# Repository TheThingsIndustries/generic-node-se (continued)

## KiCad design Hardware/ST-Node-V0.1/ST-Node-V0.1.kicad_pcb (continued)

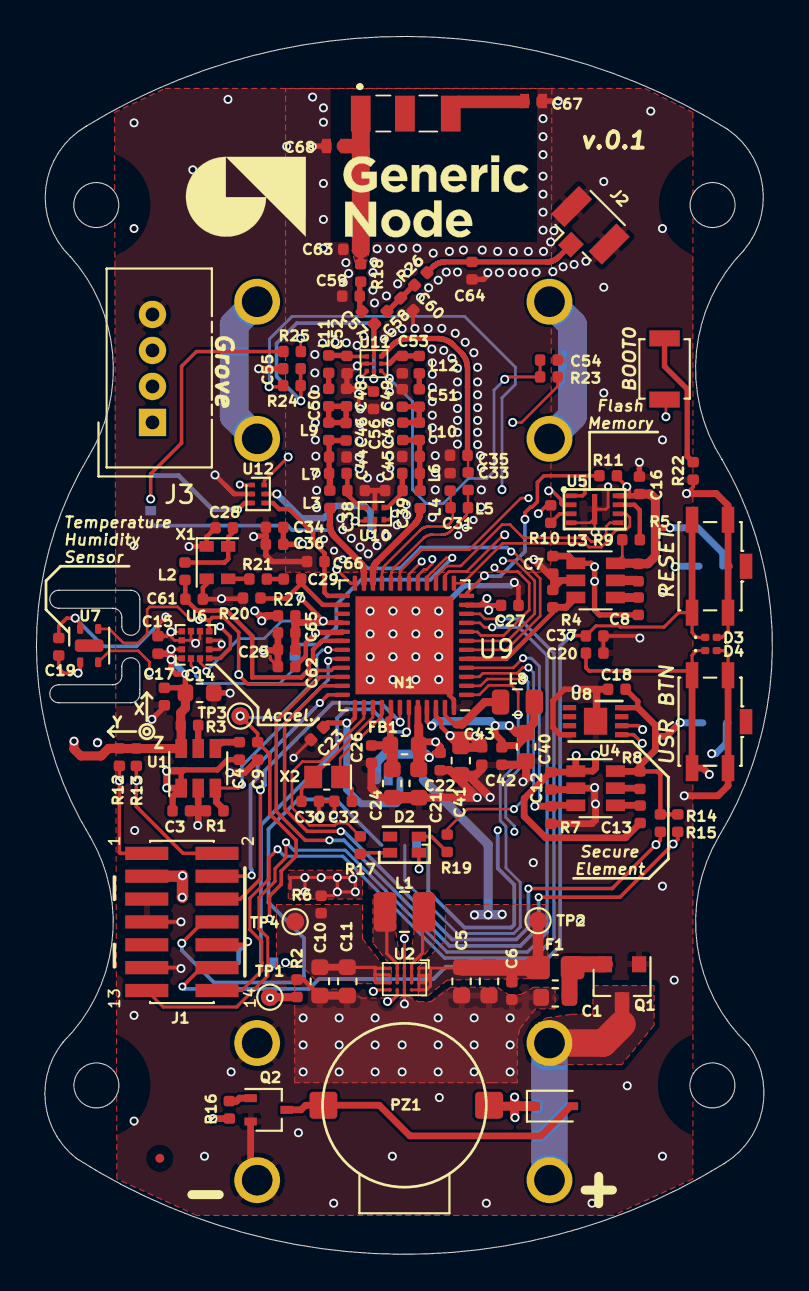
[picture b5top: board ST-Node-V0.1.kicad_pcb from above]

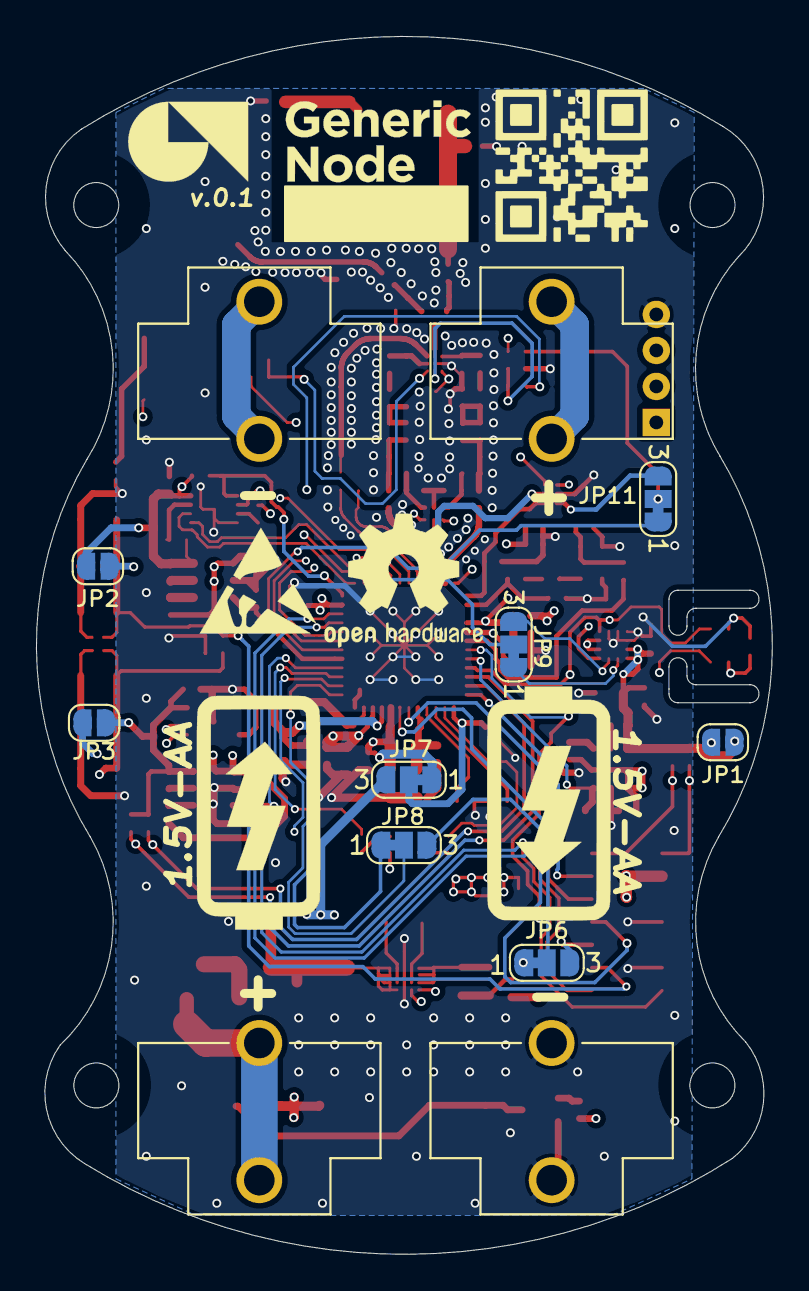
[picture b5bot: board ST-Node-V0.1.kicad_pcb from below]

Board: 4 copper layers, 40.9 x 67.7 mm, 159 parts (12 on the bottom side), 97 nets.

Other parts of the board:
J3: Grove_I2C; NS-Tech_Grove_1x04_P2mm_Vertical
R27: 0R; R_0402_1005Metric

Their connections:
/LoRa MCU/I2C1_SCL: J3.1; also elsewhere on the board
/LoRa MCU/I2C1_SDA: J3.2; also elsewhere on the board
/Peripherals/VCC_SENSORS: J3.3; also elsewhere on the board
GND: J3.4; also elsewhere on the board

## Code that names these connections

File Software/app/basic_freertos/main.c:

/** Copyright © 2021 The Things Industries B.V.
 *
 * Licensed under the Apache License, Version 2.0 (the "License");
 * you may not use this file except in compliance with the License.
 * You may obtain a copy of the License at
 *
 *     http://www.apache.org/licenses/LICENSE-2.0
 *
 * Unless required by applicable law or agreed to in writing, software
 * distributed under the License is distributed on an "AS IS" BASIS,
 * WITHOUT WARRANTIES OR CONDITIONS OF ANY KIND, either express or implied.
 * See the License for the specific language governing permissions and
 * limitations under the License.
 */

/**
 * @file main.c
 *
 * @copyright Copyright (c) 2021 The Things Industries B.V.
 *
 */

#include "app.h"
#include "cmsis_os.h"
#include "FreeRTOS_iot_log_task.h"

uint32_t osQueueMsg;
uint32_t Queue_value = 100;

/* Definitions for TxThread */
osThreadId_t TxThreadHandle;
const osThreadAttr_t TxThread_attributes = {
    .name = "TxThread",
    .priority = (osPriority_t)osPriorityBelowNormal,
    .stack_size = 512 * 4};

/* Definitions for RxThread */
osThreadId_t RxThreadHandle;
const osThreadAttr_t RxThread_attributes = {
    .name = "RxThread",
    .priority = (osPriority_t)osPriorityNormal,
    .stack_size = 512 * 4};

/* Definitions for osqueue */
osMessageQueueId_t osqueueHandle;
const osMessageQueueAttr_t osqueue_attributes = {
    .name = "osqueue"};

static void SystemClock_Config(void);
static void Error_Handler(void);

void QueueSendThread(void *argument);
void QueueReceiveThread(void *argument);

static void MX_GPIO_Init(void);

/**
  * @brief  Function implementing the TxThread thread.
  * @param  argument: Not used
  * @retval None
  */
void QueueSendThread(void *argument)
{
  for (;;)
  {
#if (GNSE_TINY_TRACER_ENABLE)
    configPRINTF(("\r\n Send a Tx msg \r\n"));
#endif
    /* Place this thread into the blocked state until it is time to run again.
       The kernel will place the MCU into the Retention low power sleep state
       when the idle thread next runs. */
    osDelay(TX_DELAY);

    /* Send to the queue - causing the queue receive thread to flash its LED.
       It should not be necessary to block on the queue send because the Rx
       thread will already have removed the last queued item. */
    osMessageQueuePut(osqueueHandle, &Queue_value, 100, 0U);
  }
}

/**
* @brief Function implementing the RxThread thread.
* @param argument: Not used
* @retval None
*/
void QueueReceiveThread(void *argument)
{
  osStatus_t status;

  for (;;)
  {
    status = osMessageQueueGet(osqueueHandle, &osQueueMsg, NULL, 100);

    if (status == osOK)
    {
#if (GNSE_TINY_TRACER_ENABLE)
      configPRINTF(("\r\n Received Rx msg \r\n"));
#endif
      if (osQueueMsg == Queue_value)
      {
        GNSE_BSP_LED_On(LED_BLUE);
        osDelay(LED_TOGGLE_DELAY);
        GNSE_BSP_LED_Off(LED_BLUE);
      }
    }
  }
}

int main(void)
{
  /* Reset of all peripherals, Initializes the Flash interface and the Systick. */
  HAL_Init();

  /* Configure the system clock */
  SystemClock_Config();

  MX_GPIO_Init();

  /* Initialize LED */
  GNSE_BSP_LED_Init(LED_BLUE);
  GNSE_BSP_LED_Init(LED_RED);

  /* Init scheduler */
  osKernelInitialize();

#if (GNSE_TINY_TRACER_ENABLE)
  /* Initialize Tracer/Logger */
  GNSE_TRACER_INIT();
  GNSE_app_printAppInfo();

  xLoggingTaskInitialize(mainLOGGING_TASK_STACK_SIZE,
                         mainLOGGING_TASK_PRIORITY,
                         mainLOGGING_MESSAGE_QUEUE_LENGTH);
#endif
  /* Create the queue(s) */
  /* creation of osqueue */
  osqueueHandle = osMessageQueueNew(1, sizeof(uint16_t), &osqueue_attributes);

  /* Create the thread(s) */
  /* creation of TxThread */
  TxThreadHandle = osThreadNew(QueueSendThread, NULL, &TxThread_attributes);

  /* creation of RxThread */
  RxThreadHandle = osThreadNew(QueueReceiveThread, NULL, &RxThread_attributes);

  /* Start scheduler */
  osKernelStart();

  while (1)
  {
    //Should never reach here
  }
}

/**
  * @brief GPIO Initialization Function
  * @param None
  * @retval None
  */
static void MX_GPIO_Init(void)
{
  GPIO_InitTypeDef GPIO_InitStruct = {0};

  /* GPIO Ports Clock Enable */
  __HAL_RCC_GPIOA_CLK_ENABLE();
  __HAL_RCC_GPIOB_CLK_ENABLE();
  __HAL_RCC_GPIOC_CLK_ENABLE();
  __HAL_RCC_GPIOH_CLK_ENABLE();

  /*Configure GPIO pins : PA14 PA12 PA15 PA13
                           PA11 PA10 PA0 PA9
                           PA6 PA1 PA3 PA2
                           PA7 PA4 PA5 PA8 */
  GPIO_InitStruct.Pin = GPIO_PIN_14|GPIO_PIN_12|GPIO_PIN_15|GPIO_PIN_13
                          |GPIO_PIN_11|GPIO_PIN_10|GPIO_PIN_0|GPIO_PIN_9
                          |GPIO_PIN_6|GPIO_PIN_1|GPIO_PIN_3|GPIO_PIN_2
                          |GPIO_PIN_7|GPIO_PIN_4|GPIO_PIN_5|GPIO_PIN_8;
  GPIO_InitStruct.Mode = GPIO_MODE_ANALOG;
  GPIO_InitStruct.Pull = GPIO_NOPULL;
  HAL_GPIO_Init(GPIOA, &GPIO_InitStruct);

  /*Configure GPIO pins : PB15 PB3 PB4 PB7
                           PB9 PB14 PB5 PB8
                           PB13 PB2 PB6 PB12
                           PB1 PB0 PB11 PB10 */
  GPIO_InitStruct.Pin = GPIO_PIN_15|GPIO_PIN_3|GPIO_PIN_4|GPIO_PIN_7
                          |GPIO_PIN_9|GPIO_PIN_14|GPIO_PIN_5|GPIO_PIN_8
                          |GPIO_PIN_13|GPIO_PIN_2|GPIO_PIN_6|GPIO_PIN_12
                          |GPIO_PIN_1|GPIO_PIN_0|GPIO_PIN_11|GPIO_PIN_10;
  GPIO_InitStruct.Mode = GPIO_MODE_ANALOG;
  GPIO_InitStruct.Pull = GPIO_NOPULL;
  HAL_GPIO_Init(GPIOB, &GPIO_InitStruct);

  /*Configure GPIO pins : PC14 PC15 PC13 PC2
                           PC3 PC5 PC1 PC0
                           PC4 PC6 */
  GPIO_InitStruct.Pin = GPIO_PIN_14|GPIO_PIN_15|GPIO_PIN_13|GPIO_PIN_2
                          |GPIO_PIN_3|GPIO_PIN_5|GPIO_PIN_1|GPIO_PIN_0
                          |GPIO_PIN_4|GPIO_PIN_6;
  GPIO_InitStruct.Mode = GPIO_MODE_ANALOG;
  GPIO_InitStruct.Pull = GPIO_NOPULL;
  HAL_GPIO_Init(GPIOC, &GPIO_InitStruct);

  /*Configure GPIO pin : PH3 */
  GPIO_InitStruct.Pin = GPIO_PIN_3;
  GPIO_InitStruct.Mode = GPIO_MODE_ANALOG;
  GPIO_InitStruct.Pull = GPIO_NOPULL;
  HAL_GPIO_Init(GPIOH, &GPIO_InitStruct);

}

/**
  * @brief System Clock Configuration
  * @retval None
  */
void SystemClock_Config(void)
{
  RCC_OscInitTypeDef RCC_OscInitStruct = {0};
  RCC_ClkInitTypeDef RCC_ClkInitStruct = {0};

  /** Configure the main internal regulator output voltage
  */
  __HAL_PWR_VOLTAGESCALING_CONFIG(PWR_REGULATOR_VOLTAGE_SCALE1);
  /** Initializes the CPU, AHB and APB busses clocks
  */
  RCC_OscInitStruct.OscillatorType = RCC_OSCILLATORTYPE_MSI;
  RCC_OscInitStruct.MSIState = RCC_MSI_ON;
  RCC_OscInitStruct.MSICalibrationValue = RCC_MSICALIBRATION_DEFAULT;
  RCC_OscInitStruct.MSIClockRange = RCC_MSIRANGE_11;
  RCC_OscInitStruct.PLL.PLLState = RCC_PLL_NONE;
  if (HAL_RCC_OscConfig(&RCC_OscInitStruct) != HAL_OK)
  {
    Error_Handler();
  }
  /** Configure the SYSCLKSource, HCLK, PCLK1 and PCLK2 clocks dividers
  */
  RCC_ClkInitStruct.ClockType = RCC_CLOCKTYPE_HCLK3 | RCC_CLOCKTYPE_HCLK | RCC_CLOCKTYPE_SYSCLK | RCC_CLOCKTYPE_PCLK1 | RCC_CLOCKTYPE_PCLK2;
  RCC_ClkInitStruct.SYSCLKSource = RCC_SYSCLKSOURCE_MSI;
  RCC_ClkInitStruct.AHBCLKDivider = RCC_SYSCLK_DIV1;
  RCC_ClkInitStruct.APB1CLKDivider = RCC_HCLK_DIV1;
  RCC_ClkInitStruct.APB2CLKDivider = RCC_HCLK_DIV1;
  RCC_ClkInitStruct.AHBCLK3Divider = RCC_SYSCLK_DIV1;

  if (HAL_RCC_ClockConfig(&RCC_ClkInitStruct, FLASH_LATENCY_2) != HAL_OK)
  {
    Error_Handler();
  }
}

/**
  * @brief  This function is executed in case of error occurrence.
  * @return None
  */
static void Error_Handler(void)
{
  while (1)
  {
  }
}

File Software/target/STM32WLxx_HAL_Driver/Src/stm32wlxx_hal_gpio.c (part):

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        active and the GPIO pins are configured in input floating mode (except JTAG
        pins).

    (#) The LSE oscillator pins OSC32_IN and OSC32_OUT can be used as general purpose
        (PC14 and PC15, respectively) when the LSE oscillator is off. The LSE has
        priority over the GPIO function.

    (#) The HSE oscillator pins OSC_IN/OSC_OUT can be used as
        general purpose PH0 and PH1, respectively, when the HSE oscillator is off.
        The HSE has priority over the GPIO function.

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
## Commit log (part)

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2020-07-06 lib: Add load switches APIs
2020-07-06 lib: Add initial battery monitoring APIs
2020-07-06 lib: Add push button control APIs
2020-07-06 lib: Add LED control functions
2020-07-06 lib: Add comments and fixes to BSP lib
2020-07-06 dev: Add cmake and build ignores
2020-07-07 dev: Add cmake windows fixes
2020-07-07 all: Add target support files
2020-07-08 all: Add STM32WL HAL files and templates
2020-07-08 dev: Add openOCD vscode launcher
2020-07-08 app, dev: Add a basic led toggling app with normal clock
2020-07-20 lib: Remove HAL lib in favour of external subtree
2020-07-20 all: Update target files (linker, conf) location and naming
2020-07-20 app: Clean-up basic LED toggle app
2020-07-20 Squashed 'Software/target/STM32WLxx_HAL_Driver/' content from commit aaf161f
    git-subtree-dir: Software/target/STM32WLxx_HAL_Driver
    git-subtree-split: aaf161f411eab041aeb2b4d424dc17327c02dacf
2020-07-21 doc: Add build guide and folder info
    doc: Fix minor spelling issues
2020-07-23 dev: Ignore VS Code files
2020-07-28 all: Add UART RX and TX support with ST advanced trace lib
2020-07-31 doc: Update with SHTC3 lib description and Basic app changes
2020-08-07 lib: Add SPI1 support functions and initialization
2020-08-07 app: Add external SPI flash basic init and basic test
2020-08-12 Squashed 'Software/target/STM32WLxx_HAL_Driver/' changes from aaf161f..504f73e
    504f73e lib: Update from CMSIS V5.0.4 to CMSIS V5.1.0
    e172617 lib: Update with STM32WL 0.7 HAL driver
    git-subtree-dir: Software/target/STM32WLxx_HAL_Driver
    git-subtree-split: 504f73e49b6d7abb054c5a5cb25cbf1b97dff7e9
2020-08-13 lib: Add float printing capability for application layer debug prints
2020-08-13 app: Add accelerometer basic read and restructured function calls
    all: Update with minor astyle fixes
2020-08-17 lib: Add TIM2 and PWM support for Buzzer
2020-08-17 lib: Add BUZZER lib
2020-08-21 lib: Support Buzzer pin reset in OFF state to reduce power consumption
2020-08-30 lib: Add ST utilities needed for a basic LoRaWAN app
2020-08-30 lib: Update USART to support waking up from Stop mode
2020-08-30 lib: Add BSP radio support and pin mapping
2020-08-30 lib: Support global object access (subGHz and USART TX DMA)
2020-09-07 app: Add basic_lorawan app
    app: Remove repeated interfaces
2020-09-07 lib: Add LPM and RTC support interfaces
    lib: Handle a compilation warning
2020-09-07 app: Improve basic apps file structure and add todos
2020-09-15 compiler: Update linker script to match V0.7 structure
2020-09-15 lib: Add ATECC608A-TNGLoRa lib
2020-09-15 basic: Add support for SE info read and restructured app
2020-09-30 dev, doc: Add battery holder Sch & PCB files
2020-09-30 compiler: Add baremetal target system calls and memory management APIs
2020-10-07 lib: Improve debug uart init
    lib: fix incorrect I2C clock assignment
    lib: Add I2C fastmode pulse
2020-10-07 app: Add minor UART and app fixes
2020-10-13 app: Add a skeleton for a basic bootloader app
2020-11-03 compiler: Add booloader and app linker scripts with configurable memory
    Linker: Add minor adjustments
2020-11-03 lib: Add internal flash write and read APIs
2020-11-03 app: Add a basic bootloader that jumps to pre-configured memory address
2020-11-05 pcb: Added latest version of the GN PCB
2020-11-09 app: Add SW jump to ST internal bootloader
2020-11-16 hw: Restructure maintained files to allow for versioning
    pcb: Remove freecad files
    doc: Update readme with new HW folder structure
2020-11-24 compiler: Add FreeRTOS CMSIS support and increased heap
2020-11-24 app: Add a basic FreeRTOS blinking LED app
2020-11-26 all: Update BSP lib naming to GNSE
2020-12-01 hw: Update latest design files and Readme
2020-12-02 hw: Readme update, relative path fixes
2020-12-09 lib: Add support HW libs for V0.2 iteration
2020-12-15 lib: Add FreeRTOS Logging Lib
2020-12-15 app: Add serial logging support to basic freertos app
2020-12-19 lib: Add support for BSP v0.2 and backward compatibility with v0.1
2020-12-22 lib: Add battery monitoring ADC APIs
2021-01-02 dev: Add docker file and update example toolchain paths
2021-01-07 dev: Add STM32CubeIDE basic apps support
2021-01-18 lib: Remove BSP support for V0.1 boards
2021-01-26 dev: Update application CMAKE with new util folder structure
2021-01-26 app,lib: Update FreeRTOS apps to use the new util structure
2021-01-26 lib: Add application layer notification to Radio driver
2021-01-26 app: Add a multithread FreeRTOS LoRaWAN application
2021-01-26 lib: Add FreeRTOS-LoRaWAN application support utilities
2021-01-26 dev: Update app STM32CubeIDE with new util structure
2021-01-26 doc: Update readme with new documentation site links and legal notice
2021-01-28 Add .clabot file
2021-01-28 Remove .clabot
2021-01-28 dev: Corrected GNSE_bsp capitalisation to match library files
2021-02-08 software: use cross.cmake as default toolchain
2021-02-10 lib: Remove 0.7 HAL subtree
2021-02-10 lib: Remove unused templates
2021-02-10 lib: Add standalone CMSIS files for cortex m0+ and cortex m4
2021-02-10 dev: Update build systems with new hal folder name and structure
2021-02-15 app: Make basic skeleton for freefall app, based on basic_lorawan
2021-02-15 app: Added freefall initialisation functions
2021-02-15 app: Added exti9-5 interrupt handler
2021-02-15 app: Added accelerometer interrupt pin definitions
2021-02-15 app: Error handling made more consistent
2021-02-15 app: Removed extra space in GNSE_bsp_gpio comments
2021-02-15 app: New message timer set after failed attempt
2021-02-15 app: Moved accelerometer GPIO init to the GNSE BSP files
2021-02-15 app: Changed payload to logging counter
2021-02-15 app: Moved port configuration to app_conf
2021-02-16 lib, app: Fix Linux compilation and minor typos
2021-02-17 app: Fix minor typos
2021-02-22 lib: Update subghz (radio driver) from v0.7 to ST official v1.0
2021-02-22 lib: Update utilities from v0.7 to ST official v1.0
2021-02-22 lib, compiler: Update target files from v0.7 to ST official v1.0
2021-02-22 lib: Fix ST v1.0 stack conflict defines and includes
2021-02-22 lib: Add radio BSP initialization compatibility with ST v1.0 stack
2021-02-22 app: Update basic_lorawan app to support ST v1.0 and LMN 4.4.4
2021-02-23 dev: Fix typos in STM32CubeIDE files
2021-02-23 dev: Update STM32CubeIDE support to reflect ST v1.0 changes
    dev: Fix Linux compilation issue
    dev: Fix linux compilation
    dev: Fix Linux compilation
2021-03-03 app,doc,dev: Add basic configuration for freefall app
    app,doc,dev: Add basic configuration for freefall app
    app: Added freefall app to app list in CMakeLists
    app: Added freefall initialisation functions
    app: Freefall config made configurable
2021-03-03 app,lib: Fix minor typos and issues
    app: Added free-fall disable function
    app: Fixed minor typos
    app: Fixed typo for STM32CubeIDE
    app: Removed unused led/Rx functions
    lib,app: Moved functions to more appropriate places
    lib: Set accelerometer priority to lowest value
2021-03-03 app: Fix accelerometer function placements and naming conventions
    app: Added ACC prefix to freefall defines
    app: Defined accelerometer return types
    app: Moved accelerometer functions to sys_app
    app: Set accelerometer function to result_t type
2021-03-03 app,lib: Fix function placement and comments
    app: Moved accelerometer GPIO init to the GNSE BSP files
    app: Moved port configuration to app_conf
    app: Changed payload to logging counter
    app: New message timer set after failed attempt
    app: Fixed some comments
    app: Added comments for the register initialisation
2021-03-10 app: Simplify SW based LoRaWAN applications EUI and Key configuration
2021-03-10 doc: Update applications description and add configuration writeup
2021-03-16 lib: Add ATECC608-TNGLORA stack support
2021-03-16 app,dev: Add secure_element_lorawan app
2021-03-16 doc: Add secure_element_lorawan app description
2021-03-22 app,lib: Add basic interfaces for GNSE
2021-03-24 dev: Add faster CMakelists for development
2021-03-25 lib: Add GNSE Tracer (TINY and Advanced)
2021-03-25 app: Update freertos_lorawan duty cycle handling after Stack update
2021-03-25 lib: Adapt all libs to use GNSE Tracer (TINY and ADVANCED))
2021-03-25 app,dev: Update apps to use GNSE advanced tracer
2021-03-25 doc: Fix minor spelling issues found with system tracer PR
2021-04-02 lib: Fix tiny_tracer headers
2021-04-19 lib,app: Add downlink handler with buzzer tunes
2021-04-19 lib, doc: Improve MX25R16 flash APIs and add HAL file system support
    lib: Add external flash HAL and support for file system
    doc: Add minor spelling fixes and todos
    lib: Improve spelling and formatting
2021-04-19 lib: Add SPIFFS library to be able to use file system on external flash
2021-04-23 compiler: Add startup and linker support for threadx (AzureRTOS)
2021-04-23 app, doc, dev: Add basic_azurertos app
    app: Improve basic_azurertos app comments
    doc: Add basic_azurertos config link
    dev: Add basic_azurertos STM32CubeIDE support
2021-04-23 app: Add GNSE certification app with AT commands
2021-04-28 doc: Update documentation URL
2021-06-08 dev,lib: Add SE RNG support
2021-06-09 app,doc : Add sensors_lorawan application and an example payload decoder
2021-06-23 doc: Add README for basic, basic_lorawan, freefall_lorawan apps
2021-06-25 lib: Fix stack handling of multicast keys generation defaulting to 1.1
2021-06-25 lib: Update FragDecoder to support interoperability test mode
2021-06-25 lib: Remove McGroupBitMask check that causes frag drops
    This check for McGroupBitMask is not functional in the original LMN stack, see https://github.com/Lora-net/LoRaMac-node/blob/57806121493588220ab9d06e87201a02a611e99e/src/apps/LoRaMac/common/LmHandler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
2021-06-28 app,dev: Add app_template application
2021-07-01 app: Increase FreeRTOS downlink retrieval window
2021-07-08 lib: Improve the HAL GNSE LPM and remove abstract LPM utility
2021-07-13 app, lib: Update apps to use improved GNSE LPM
2021-07-14 app,lib: Add common system clk function
2021-07-19 app: Improve free fall low power current to ~44uA
2021-08-17 app, lib, dev: Remove LW stack lib dependency and improve structure
2021-08-24 doc: Add generic-node License
2021-09-08 dev: Improve CMAKE build system and adapt for new common app APIs
2021-09-08 dev: Add STM32CubeIDE support for common app APIs and app name
2021-09-08 app: Add app info log for all applications
2021-10-11 doc: Add SW architecture diagram
2021-10-11 app: Add accelerometer reading delay to basic app
2021-10-25 docs: Add Doxygen config file and generation guideline
2021-11-01 app: Improve production app join flow and LEDs notification sysrtem
2021-11-03 dev: Remove outdated and unmaintained CMake files
2021-11-08 app: Add heartbeat message
2021-11-10 app: Add IWDG
2021-11-10 app: Add Downlink handlers
2021-11-12 add uair modules
2021-11-16 GNSE: allow APP to be defined externally
2021-11-16 GNSE: skip compiler check, it often fails because it cannot link executables
2021-11-16 Add MSP initialization prototype
2021-11-16 Add syscall prototypes to avoid compiler warnings
2021-11-16 SHTC3: update driver to use new HAL/BSP backend
2021-11-16 Sync submodules
2021-11-16 Update branch
2021-11-18 build: add HAVE_LTO define to overcome compiler limitations
2021-11-18 STM32HAL: enable LPTIM
2021-11-18 GCC: some versions have issues in keeping interrupt handlers when LTO is used, due to "weak" attachment. This disables (conditionally) weak definitions for the interrupt handlers.
2021-11-18 updated submodules
2021-11-20 SHTC3: fix constant
2021-11-24 updated submodule
2021-12-06 HAL: activate hardware RNG
2022-01-06 hw: Migrate sch and pcb files to KiCad v6
2022-01-07 sch, doc: Eev update
2022-03-07 hostmode: add hostmode support
2022-03-15 hostmode: define MCU properly
2022-03-19 Add HOST_ARCH
2022-03-20 HAL: use HW 128 divider for LSI (generates input for IWDG)
2022-03-27 Fix hostmode for APPLE host
    - fixed wrong logic
2022-03-31 app: Add LED indication, button press
2022-04-04 app: Add sensor sample error handling to avoid NULL values in uplinks
2022-08-04 fix: TCXO control voltage setting bug
2022-09-19 fix: LoRaWAN sensors SE app
    Fix: App conf file
    fix: LoRaWAN sensors SE app
2022-09-20 hw: Adding updated BOM files by Arrow
2022-10-04 app: Add note to app readme that default compilation is with keys from config
